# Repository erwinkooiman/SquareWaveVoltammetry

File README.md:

# SquareWaveVoltammetry
miniaturized potentiostat with web interface

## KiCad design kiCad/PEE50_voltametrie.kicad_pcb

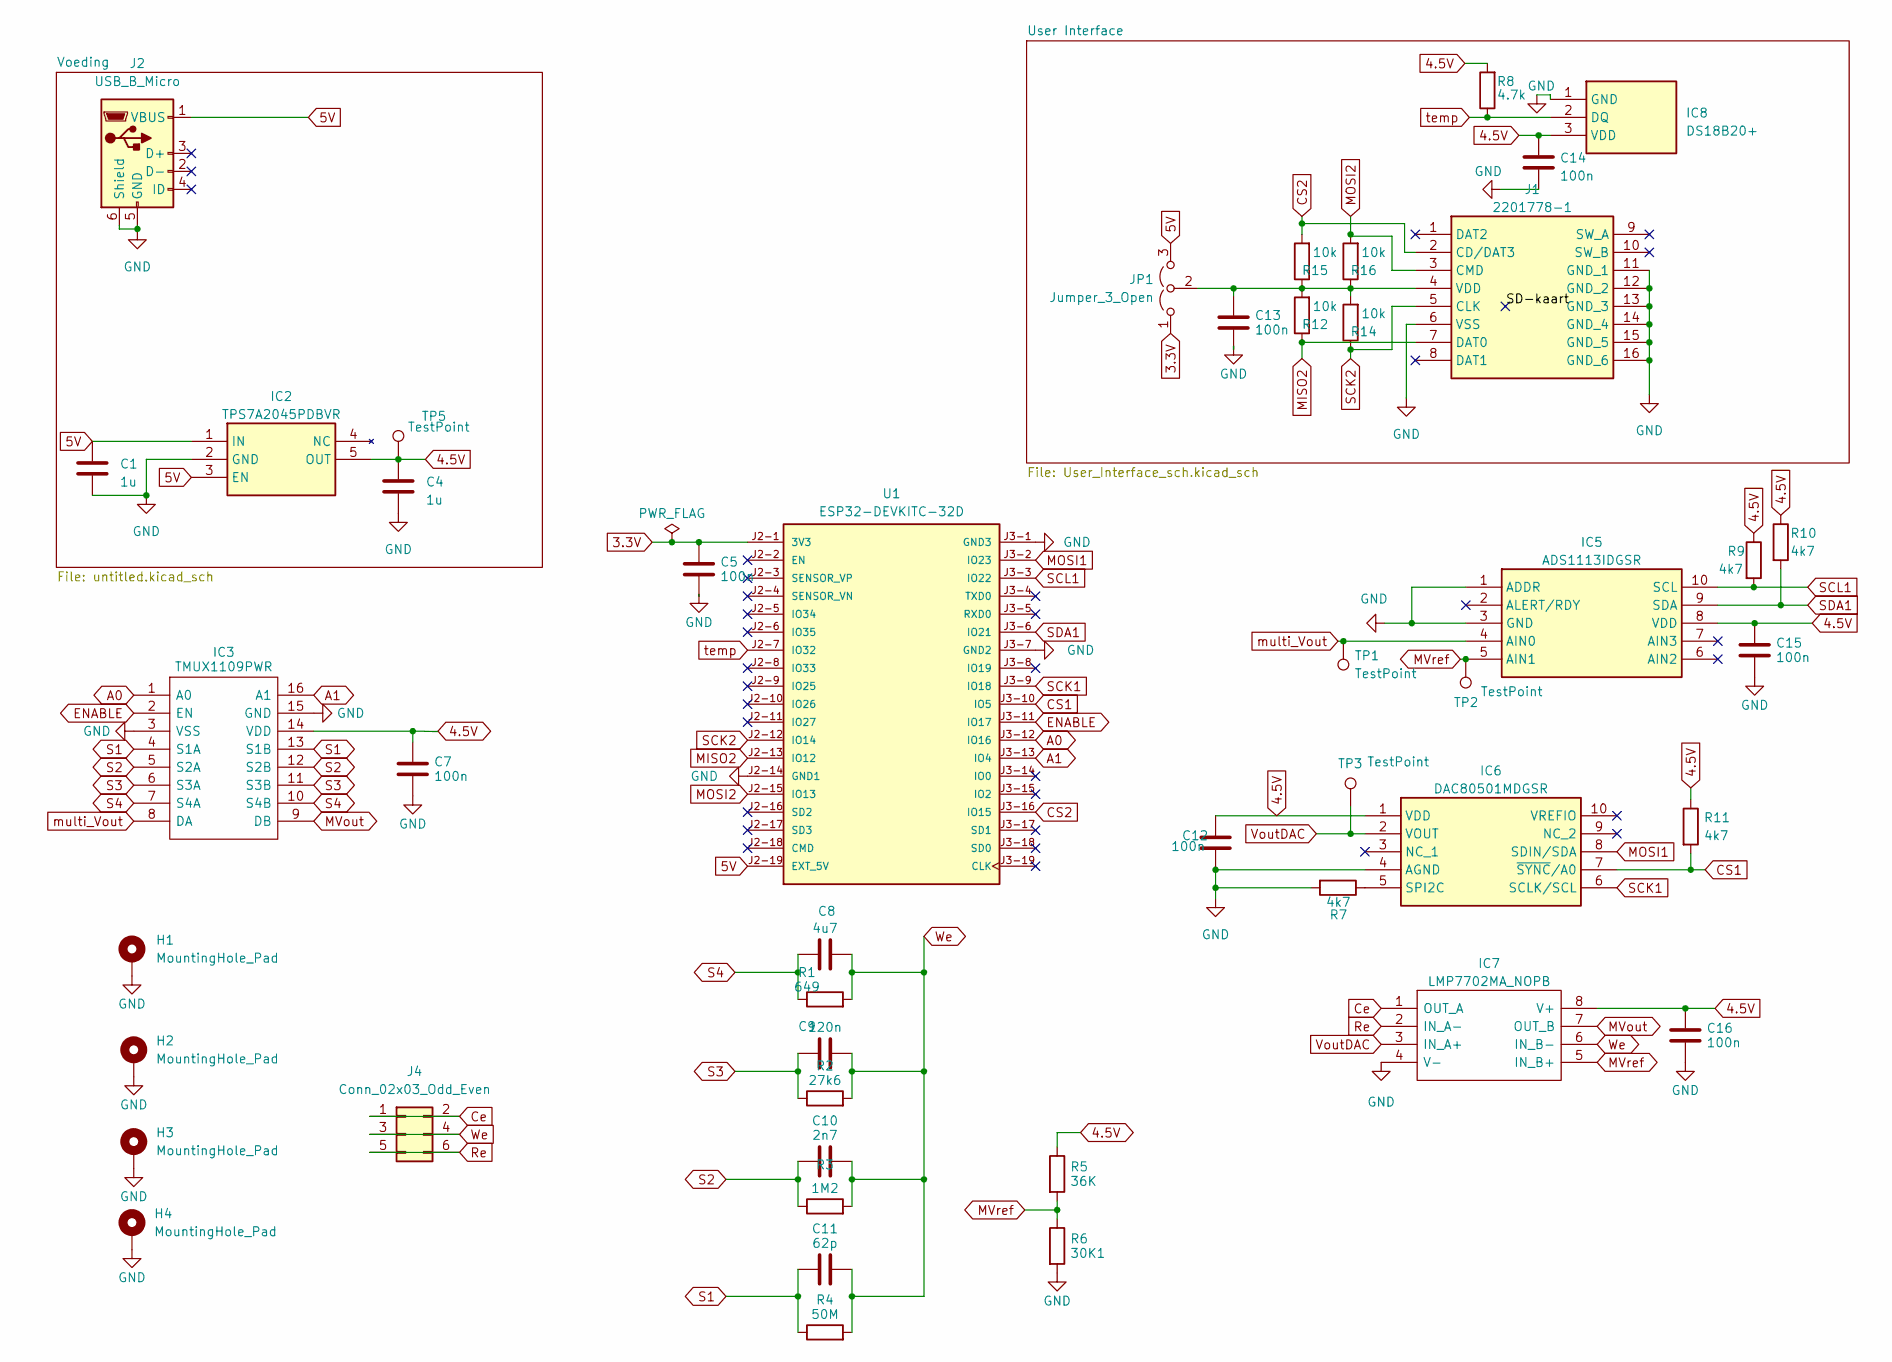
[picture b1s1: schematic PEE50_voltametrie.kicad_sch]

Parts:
C1, C4: 1u; C_0805_2012Metric_Pad1.18x1.45mm_HandSolder
C5, C7, C12, C13, C14, C15, C16: 100n; C_0805_2012Metric_Pad1.18x1.45mm_HandSolder
C8: 4u7; C_0805_2012Metric_Pad1.18x1.45mm_HandSolder
C9: 120n; C_0805_2012Metric_Pad1.18x1.45mm_HandSolder
C10: 2n7; C_0805_2012Metric_Pad1.18x1.45mm_HandSolder
C11: 62p; C_0805_2012Metric_Pad1.18x1.45mm_HandSolder
H1, H2, H3, H4: MountingHole_Pad; MountingHole_3.2mm_M3_DIN965_Pad
IC2: TPS7A2045PDBVR; SOT95P280X145-5N; Manufacturer_Part_Number TPS7A2045PDBVR; Mouser Part Number 595-TPS7A2045PDBVR
IC3: TMUX1109PWR; SOP65P640X120-16N; Manufacturer_Part_Number TMUX1109PWR; Mouser Part Number 595-TMUX1109PWR
IC5: ADS1113IDGSR; SOP50P490X110-10N; Manufacturer_Part_Number ADS1113IDGSR; Mouser Part Number 595-ADS1113IDGSR
IC6: DAC80501MDGSR; SOP50P490X110-10N; Manufacturer_Part_Number DAC80501MDGSR; Mouser Part Number 595-DAC80501MDGSR
IC7: LMP7702MA_NOPB; SOIC127P600X175-8N; Manufacturer_Part_Number LMP7702MA/NOPB; Mouser Part Number 926-LMP7702MA/NOPB
IC8: DS18B20+; DS18B20; Manufacturer_Part_Number DS18B20+; Mouser Part Number 700-DS18B20+
J1: 2201778-1; 22017781; Manufacturer_Part_Number 2201778-1; Mouser Part Number 571-2201778-1
J2: USB_B_Micro; USB_Micro-B_Amphenol_10104110_Horizontal
J4: Conn_02x03_Odd_Even; PinHeader_2x03_P2.54mm_Horizontal
JP1: Jumper_3_Open; PinHeader_1x03_P2.54mm_Vertical
R1: 649; R_0805_2012Metric_Pad1.20x1.40mm_HandSolder
R2: 27k6; R_0805_2012Metric_Pad1.20x1.40mm_HandSolder
R3: 1M2; R_0805_2012Metric_Pad1.20x1.40mm_HandSolder
R4: 50M; R_0805_2012Metric_Pad1.20x1.40mm_HandSolder
R5: 36K; R_0805_2012Metric_Pad1.20x1.40mm_HandSolder
R6: 30K1; R_0805_2012Metric_Pad1.20x1.40mm_HandSolder
R7, R9, R10, R11: 4k7; R_0805_2012Metric_Pad1.20x1.40mm_HandSolder
R8: 4.7k; R_0805_2012Metric_Pad1.20x1.40mm_HandSolder
R12, R14, R15, R16: 10k; R_0805_2012Metric_Pad1.20x1.40mm_HandSolder
TP1, TP2, TP3, TP5: TestPoint; TestPoint_Pad_D1.0mm
U1: ESP32-DEVKITC-32D; MODULE_ESP32-DEVKITC-32D; PARTREV V4

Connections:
3.3V: C5.1, JP1.1 (A), U1.J2-1 (3V3)
4.5V: C4.1, C7.1, C12.1, C14.1, C15.1, C16.1, IC2.5 (OUT), IC3.14 (VDD), IC5.8 (VDD), IC6.1 (VDD), IC7.8 (V+), IC8.3 (VDD), R5.1, R8.2, R9.1, R10.1, R11.1, TP5.1
5V: C1.1, IC2.1 (IN), IC2.3 (EN), J2.1 (VBUS), JP1.3 (B), U1.J2-19 (EXT_5V)
A0: IC3.1 (A0), U1.J3-12 (IO16)
A1: IC3.16 (A1), U1.J3-13 (IO4)
CS1: IC6.7 (~SYNC/A0), R11.2, U1.J3-10 (IO5)
CS2: J1.2 (CD/DAT3), R15.2, U1.J3-16 (IO15)
Ce: IC7.1 (OUT_A), J4.1, J4.2
ENABLE: IC3.2 (EN), U1.J3-11 (IO17)
GND: C1.2, C4.2, C5.2, C7.2, C12.2, C13.2, C14.2, C15.2, C16.2, H1.1, H2.1, H3.1, H4.1, IC2.2 (GND), IC3.3 (VSS), IC3.15 (GND), IC5.1 (ADDR), IC5.3 (GND), IC6.4 (AGND), IC7.4 (V-), IC8.1 (GND), J1.6 (VSS), J1.11 (GND_1), J1.12 (GND_2), J1.13 (GND_3), J1.14 (GND_4), J1.15 (GND_5), J1.16 (GND_6), J2.5 (GND), J2.6 (Shield), R6.2, R7.2, U1.J2-14 (GND1), U1.J3-1 (GND3), U1.J3-7 (GND2)
MISO2: J1.7 (DAT0), R12.1, U1.J2-13 (IO12)
MOSI1: IC6.8 (SDIN/SDA), U1.J3-2 (IO23)
MOSI2: J1.3 (CMD), R16.2, U1.J2-15 (IO13)
MVout: IC3.9 (DB), IC7.7 (OUT_B)
MVref: IC5.5 (AIN1), IC7.5 (IN_B+), R5.2, R6.1, TP2.1
unnamed: IC6.5 (SPI2C), R7.1
unnamed: C13.1, J1.4 (VDD), JP1.2 (C), R12.2, R14.2, R15.1, R16.1
Re: IC7.2 (IN_A-), J4.5, J4.6
S1: C11.1, IC3.4 (S1A), IC3.13 (S1B), R4.1
S2: C10.1, IC3.5 (S2A), IC3.12 (S2B), R3.1
S3: C9.1, IC3.6 (S3A), IC3.11 (S3B), R2.1
S4: C8.1, IC3.7 (S4A), IC3.10 (S4B), R1.1
SCK1: IC6.6 (SCLK/SCL), U1.J3-9 (IO18)
SCK2: J1.5 (CLK), R14.1, U1.J2-12 (IO14)
SCL1: IC5.10 (SCL), R9.2, U1.J3-3 (IO22)
SDA1: IC5.9 (SDA), R10.2, U1.J3-6 (IO21)
VoutDAC: IC6.2 (VOUT), IC7.3 (IN_A+), TP3.1
We: C8.2, C9.2, C10.2, C11.2, IC7.6 (IN_B-), J4.3, J4.4, R1.2, R2.2, R3.2, R4.2
multi_Vout: IC3.8 (DA), IC5.4 (AIN0), TP1.1
temp: IC8.2 (DQ), R8.1, U1.J2-7 (IO32)

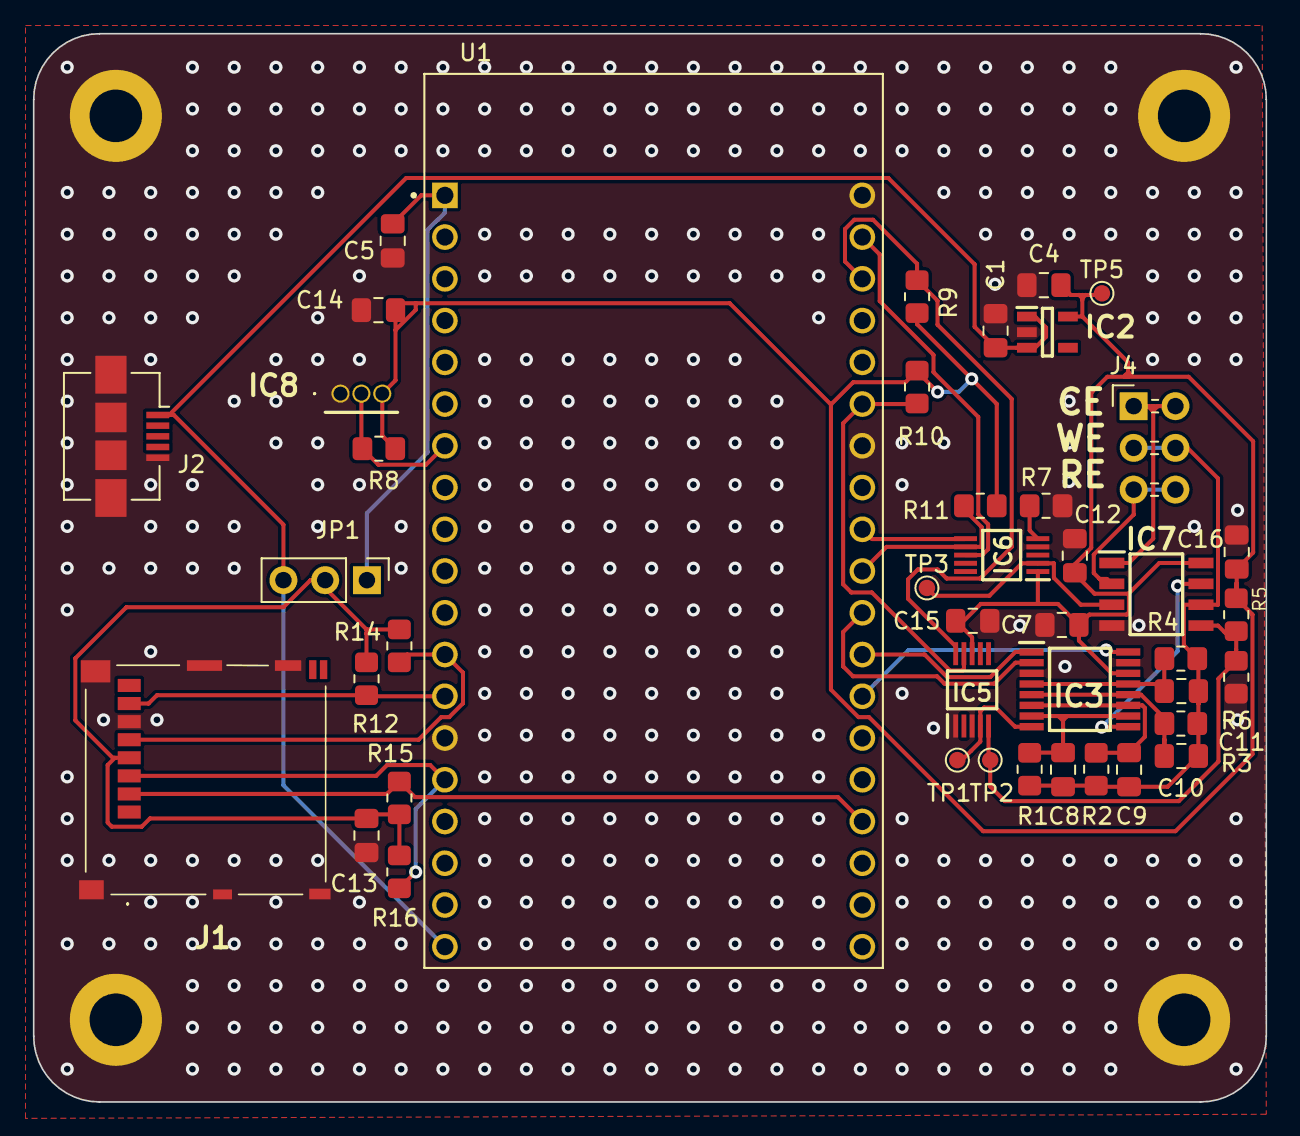
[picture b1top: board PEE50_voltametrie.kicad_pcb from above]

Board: 2 copper layers, 75.0 x 65.0 mm, 48 parts (1 on the bottom side), 30 nets.

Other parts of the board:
G1: LOGO; hogeschool_rotterdam_logo

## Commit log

2023-06-05 first commit
    creates a access point. Use web interface to set parameters and start measurements.
2023-06-05 removed unecessary printouts
2023-06-05 added comments and changed a few variable names to english
2023-06-06 added kicad map
2023-06-06 small fix
2023-06-06 Version 1 kicad files
2023-06-06 Version 2 kicad files
    Before traces are added
2023-06-06 added temperature sensor
2023-06-06 Version 3 kicad
    Withoud 3.3V regulator not needed because of devkit
2023-06-06 layout aangepast
2023-06-07 Sd kaart lib toegevoegd
2023-06-12 added SD card logger (not tested jet)
2023-06-12 version without SD but with data stream excel
2023-06-12 check if SD card is detected, removed save button
2023-06-13 tested code
2023-06-13 Update SWV.ino
    small fix
2023-06-14 SPI pin changes
2023-06-14 final pcb update
2023-06-19 moved sd card in seperate function
2023-06-22 fixed sd card upload bug
2023-06-27 potential now resets when finished
